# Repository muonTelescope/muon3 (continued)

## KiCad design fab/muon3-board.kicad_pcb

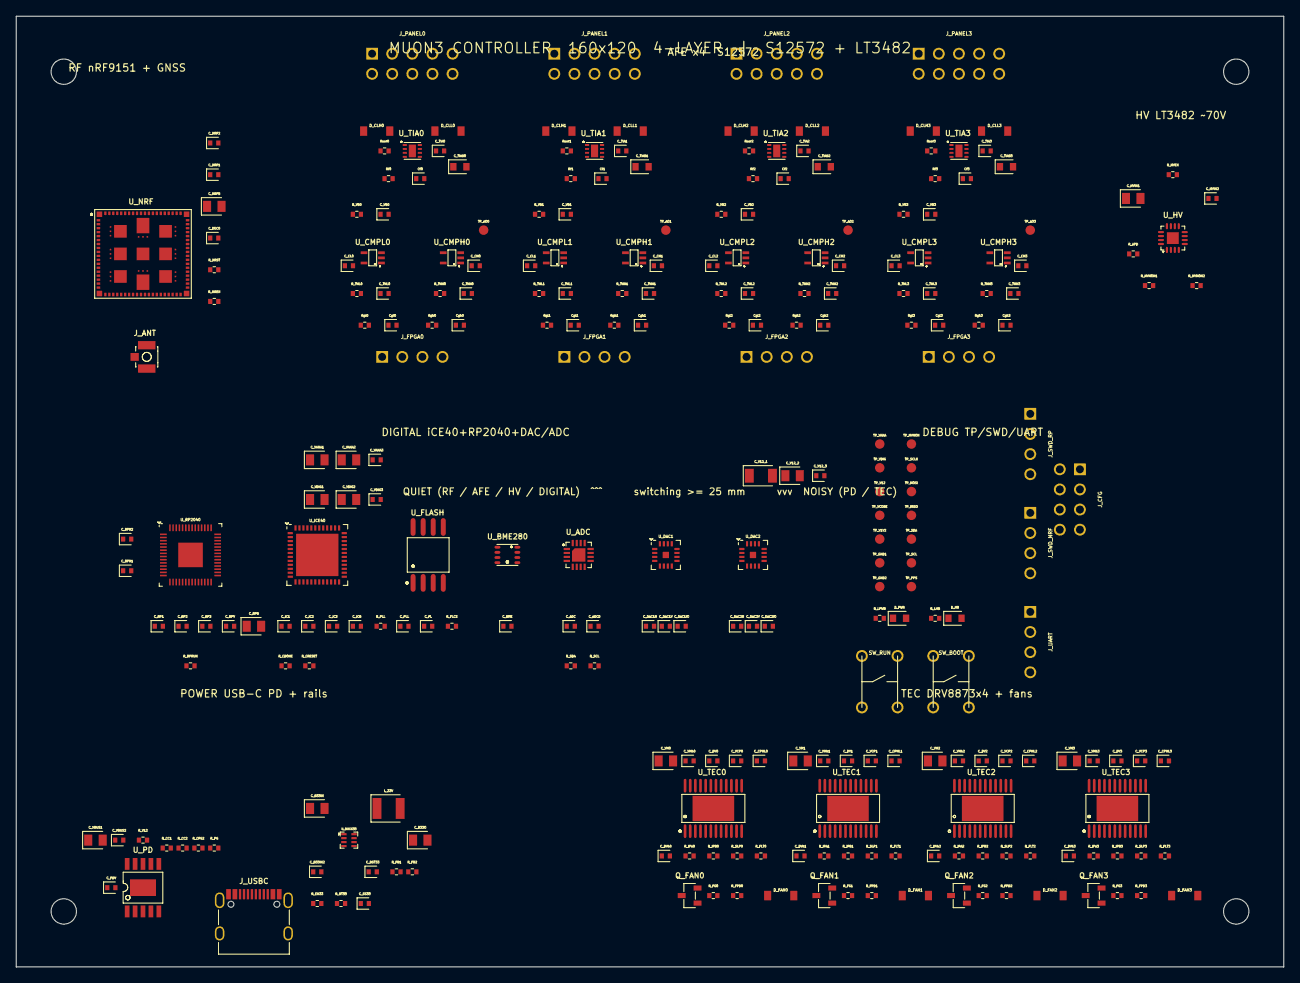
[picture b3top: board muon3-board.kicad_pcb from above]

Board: 4 copper layers, 160.0 x 120.0 mm, 265 parts (0 on the bottom side), 156 nets, no tracks yet.

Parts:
C_ADC: 100nF; capacitor_0402
C_ADCD: 1uF; capacitor_0402
C_B33IN: 10uF; capacitor_0805
C_B33IN2: 100nF; capacitor_0402
C_B33O: 22uF; capacitor_0805
C_BME: 100nF; capacitor_0402
C_BST33: 100nF; capacitor_0402
C_CH0, C_CH1, C_CH2, C_CH3: 100nF; capacitor_0402
C_CL0, C_CL1, C_CL2, C_CL3: 100nF; capacitor_0402
C_CPHL0, C_CPHL1, C_CPHL2, C_CPHL3: 47nF; capacitor_0402
C_DAC1IO, C_DAC1V, C_DAC2IO, C_DAC2V: 100nF; capacitor_0402
C_DAC1R, C_DAC2R: 1uF; capacitor_0402
C_DEC0: 100nF; capacitor_0402
C_DV0, C_DV1, C_DV2, C_DV3: 1uF; capacitor_0402
C_DVh0, C_DVh1, C_DVh2, C_DVh3: 100nF; capacitor_0402
C_FL: 100nF; capacitor_0402
C_HVIN1: 10uF; capacitor_0805
C_HVIN2: 100nF; capacitor_0402
C_IC1, C_IC2, C_IC3: 100nF; capacitor_0402
C_ICB: 1uF; capacitor_0402
C_NRF1, C_NRF2: 100nF; capacitor_0402
C_NRFB: 4.7uF; capacitor_0805
C_PDV: 100nF; capacitor_0402
C_PLL: 100nF; capacitor_0402
C_RP1, C_RP2, C_RP3: 100nF; capacitor_0402
C_RPB: 10uF; capacitor_0805
C_RPV: 1uF; capacitor_0402
C_RPX1, C_RPX2: 18pF; capacitor_0402
C_SS33: 10nF; capacitor_0402
C_THH0, C_THH1, C_THH2, C_THH3: 100nF; capacitor_0402
C_THL0, C_THL1, C_THL2, C_THL3: 100nF; capacitor_0402
C_TIA0, C_TIA1, C_TIA2, C_TIA3: 100nF; capacitor_0402
C_TIAB0, C_TIAB1, C_TIAB2, C_TIAB3: 2.2uF; capacitor_0603
C_V12_1: 22uF; capacitor_1206
C_V12_2: 10uF; capacitor_0805
C_V12_3: 100nF; capacitor_0402
C_VANA1, C_VANA2: 10uF; capacitor_0805
C_VANA3: 100nF; capacitor_0402
C_VB0, C_VB1, C_VB2, C_VB3: 100nF; capacitor_0402
C_VBUS1: 10uF; capacitor_0805
C_VBUS2: 100nF; capacitor_0402
C_VCP0, C_VCP1, C_VCP2, C_VCP3: 1uF; capacitor_0402
C_VDIG1, C_VDIG2: 10uF; capacitor_0805
C_VDIG3: 100nF; capacitor_0402
C_VM0, C_VM1, C_VM2, C_VM3: 10uF; capacitor_0805
C_VMh0, C_VMh1, C_VMh2, C_VMh3: 100nF; capacitor_0402
Cf0, Cf1, Cf2, Cf3: 1.5pF; capacitor_0402
Cgh0, Cgh1, Cgh2, Cgh3: 6pF; capacitor_0402
Cgl0, Cgl1, Cgl2, Cgl3: 6pF; capacitor_0402
D_CLH0, D_CLH1, D_CLH2, D_CLH3: D; diode_sod123
D_CLL0, D_CLL1, D_CLL2, D_CLL3: D; diode_sod123
D_FAN0, D_FAN1, D_FAN2, D_FAN3: D; diode_sod123
D_HB: LED; led_0603
D_PWR: LED; led_0603
J_ANT: BWU_FL_IPEX1
J_CFG: J_CFG; pin_header_pinrow8_nopinlabels_rows2
J_FPGA0: J_FPGA0; pin_header_pinrow4_nopinlabels
J_FPGA1: J_FPGA1; pin_header_pinrow4_nopinlabels
J_FPGA2: J_FPGA2; pin_header_pinrow4_nopinlabels
J_FPGA3: J_FPGA3; pin_header_pinrow4_nopinlabels
J_PANEL0: J_PANEL0; pin_header_pinrow10_nopinlabels_female_rows2
J_PANEL1: J_PANEL1; pin_header_pinrow10_nopinlabels_female_rows2
J_PANEL2: J_PANEL2; pin_header_pinrow10_nopinlabels_female_rows2
J_PANEL3: J_PANEL3; pin_header_pinrow10_nopinlabels_female_rows2
J_SWD_NRF: J_SWD_NRF; pin_header_pinrow4_nopinlabels
J_SWD_RP: J_SWD_RP; pin_header_pinrow4_nopinlabels
J_UART: J_UART; pin_header_pinrow4_nopinlabels
J_USBC: TYPE_C_31_M_12
L_33V: 4.7µH; inductor_1210
Q_FAN0, Q_FAN1, Q_FAN2, Q_FAN3: AO3400A
R_APD: 20Ω; resistor_res0402
R_CC1, R_CC2: 5.1kΩ; resistor_res0402
R_CDONE: 10kΩ; resistor_res0402
R_CFG2: 6.8kΩ; resistor_res0402
R_CRESET: 10kΩ; resistor_res0402
R_EN33: 100kΩ; resistor_res0402
R_FB1: 100kΩ; resistor_res0402
R_FB2: 32kΩ; resistor_res0402
R_FG0, R_FG1, R_FG2, R_FG3: 100Ω; resistor_res0402
R_FLCS: 10kΩ; resistor_res0402
R_FLT0, R_FLT1, R_FLT2, R_FLT3: 47kΩ; resistor_res0402
R_FPD0, R_FPD1, R_FPD2, R_FPD3: 10kΩ; resistor_res0402
R_HVEN: 100kΩ; resistor_res0402
R_HVMON1: 2MΩ; resistor_res0402
R_HVMON2: 51kΩ; resistor_res0402
R_IPA0, R_IPA1, R_IPA2, R_IPA3: 1.5kΩ; resistor_res0402
R_IPB0, R_IPB1, R_IPB2, R_IPB3: 1.5kΩ; resistor_res0402
R_LHB: 330Ω; resistor_res0402
R_LPWR: 1kΩ; resistor_res0402
R_NREN: 100kΩ; resistor_res0402
R_NRST: 10kΩ; resistor_res0402
R_PG: 10kΩ; resistor_res0402
R_PLL: 100Ω; resistor_res0402
R_RPRUN: 10kΩ; resistor_res0402
R_RT33: 100kΩ; resistor_res0402
R_SCL: 4.7kΩ; resistor_res0402
R_SDA: 4.7kΩ; resistor_res0402
R_SLP0, R_SLP1, R_SLP2, R_SLP3: 100kΩ; resistor_res0402
R_THH0, R_THH1, R_THH2, R_THH3: 1kΩ; resistor_res0402
R_THL0, R_THL1, R_THL2, R_THL3: 1kΩ; resistor_res0402
R_V12: 0Ω; resistor_res0402
R_VB0, R_VB1, R_VB2, R_VB3: 1kΩ; resistor_res0402
Rf0, Rf1, Rf2, Rf3: 15kΩ; resistor_res0402
Rgh0, Rgh1, Rgh2, Rgh3: 33Ω; resistor_res0402
Rgl0, Rgl1, Rgl2, Rgl3: 33Ω; resistor_res0402
Rser0, Rser1, Rser2, Rser3: 10Ω; resistor_res0402
SW_BOOT: SW_BOOT; push_button_pushbutton
SW_RUN: SW_RUN; push_button_pushbutton
TP_AO0: TP_AO0; test_point_smtpad_circle_d1.2
TP_AO1: TP_AO1; test_point_smtpad_circle_d1.2
TP_AO2: TP_AO2; test_point_smtpad_circle_d1.2
TP_AO3: TP_AO3; test_point_smtpad_circle_d1.2
TP_GND1: TP_GND1; test_point_smtpad_circle_d1.2
TP_GND2: TP_GND2; test_point_smtpad_circle_d1.2
TP_HVMON: TP_HVMON; test_point_smtpad_circle_d1.2
TP_MISO: TP_MISO; test_point_smtpad_circle_d1.2
TP_MOSI: TP_MOSI; test_point_smtpad_circle_d1.2
TP_PPS: TP_PPS; test_point_smtpad_circle_d1.2
TP_SCL: TP_SCL; test_point_smtpad_circle_d1.2
TP_SCLK: TP_SCLK; test_point_smtpad_circle_d1.2
TP_SDA: TP_SDA; test_point_smtpad_circle_d1.2
TP_V1V2: TP_V1V2; test_point_smtpad_circle_d1.2
TP_V12: TP_V12; test_point_smtpad_circle_d1.2
TP_VANA: TP_VANA; test_point_smtpad_circle_d1.2
TP_VCORE: TP_VCORE; test_point_smtpad_circle_d1.2
TP_VDIG: TP_VDIG; test_point_smtpad_circle_d1.2
U_ADC: ADS7128IRTER
U_BME280: BME280
U_BUCK33: TPS62933DRLR
U_CMPH0, U_CMPH1, U_CMPH2, U_CMPH3: TLV3601DCKR
U_CMPL0, U_CMPL1, U_CMPL2, U_CMPL3: TLV3601DCKR
U_DAC1, U_DAC2: DAC80508MRTER
U_FLASH: W25Q128JVSIQ
U_HV: LT3482EUD_TRPBF
U_ICE40: ICE40UP5K_SG48I
U_NRF: nRF9151_LACA_R7
U_PD: CH224K
U_RP2040: RP2040
U_TEC0, U_TEC1, U_TEC2, U_TEC3: DRV8873HPWPR
U_TIA0, U_TIA1, U_TIA2, U_TIA3: OPA858IDSGR

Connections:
ADC_DECAP: C_ADCD.1, U_ADC.8
AOUT0: TP_AO0.1, U_CMPH0.3, U_CMPL0.3, U_TIA0.6
AOUT1: TP_AO1.1, U_CMPH1.3, U_CMPL1.3, U_TIA1.6
AOUT2: TP_AO2.1, U_CMPH2.3, U_CMPL2.3, U_TIA2.6
AOUT3: TP_AO3.1, U_CMPH3.3, U_CMPL3.3, U_TIA3.6
BST33: C_BST33.1, U_BUCK33.6
CC1: J_USBC.6, R_CC1.1, U_PD.7
CC2: J_USBC.12, R_CC2.1, U_PD.6
CMPH0: Rgh0.1, U_CMPH0.1
CMPH1: Rgh1.1, U_CMPH1.1
CMPH2: Rgh2.1, U_CMPH2.1
CMPH3: Rgh3.1, U_CMPH3.1
CMPL0: Rgl0.1, U_CMPL0.1
CMPL1: Rgl1.1, U_CMPL1.1
CMPL2: Rgl2.1, U_CMPL2.1
CMPL3: Rgl3.1, U_CMPL3.1
CPH0: C_CPHL0.1, U_TEC0.22
CPH1: C_CPHL1.1, U_TEC1.22
CPH2: C_CPHL2.1, U_TEC2.22
CPH3: C_CPHL3.1, U_TEC3.22
CPL0: C_CPHL0.2, U_TEC0.23
CPL1: C_CPHL1.2, U_TEC1.23
CPL2: C_CPHL2.2, U_TEC2.23
CPL3: C_CPHL3.2, U_TEC3.23
DAC1_CS: U_DAC1.12, U_RP2040.28
DAC1_O3: C_DAC1R.1, U_DAC1.1
DAC2_CS: U_DAC2.12, U_RP2040.31
DAC2_O3: C_DAC2R.1, U_DAC2.1
DVDD0: C_DV0.1, C_DVh0.1, R_FLT0.1, R_SLP0.1, U_TEC0.1
DVDD1: C_DV1.1, C_DVh1.1, R_FLT1.1, R_SLP1.1, U_TEC1.1
DVDD2: C_DV2.1, C_DVh2.1, R_FLT2.1, R_SLP2.1, U_TEC2.1
DVDD3: C_DV3.1, C_DVh3.1, R_FLT3.1, R_SLP3.1, U_TEC3.1
EN33: R_EN33.2, U_BUCK33.2
FANG0: Q_FAN0.1, R_FG0.2, R_FPD0.1
FANG1: Q_FAN1.1, R_FG1.2, R_FPD1.1
FANG2: Q_FAN2.1, R_FG2.2, R_FPD2.1
FANG3: Q_FAN3.1, R_FG3.2, R_FPD3.1
FANN0: D_FAN0.1, J_PANEL0.10, Q_FAN0.3
FANN1: D_FAN1.1, J_PANEL1.10, Q_FAN1.3
FANN2: D_FAN2.1, J_PANEL2.10, Q_FAN2.3
FANN3: D_FAN3.1, J_PANEL3.10, Q_FAN3.3
FAULT0: R_FLT0.2, U_TEC0.2
FAULT1: R_FLT1.2, U_TEC1.2
FAULT2: R_FLT2.2, U_TEC2.2
FAULT3: R_FLT3.2, U_TEC3.2
FB0: Cf0.1, Rf0.1, U_TIA0.1
FB1: Cf1.1, Rf1.1, U_TIA1.1
FB2: Cf2.1, Rf2.1, U_TIA2.1
FB3: Cf3.1, Rf3.1, U_TIA3.1
FB33: R_FB1.2, R_FB2.1, U_BUCK33.8
FLASH_CS: R_FLCS.2, SW_BOOT.1, U_FLASH.1, U_RP2040.56
FPAH0: Cgh0.1, J_FPGA0.2, Rgh0.2, U_ICE40.47
FPAH1: Cgh1.1, J_FPGA1.2, Rgh1.2, U_ICE40.45
FPAH2: Cgh2.1, J_FPGA2.2, Rgh2.2, U_ICE40.4
FPAH3: Cgh3.1, J_FPGA3.2, Rgh3.2, U_ICE40.6
FPAL0: Cgl0.1, J_FPGA0.1, Rgl0.2, U_ICE40.46
FPAL1: Cgl1.1, J_FPGA1.1, Rgl1.2, U_ICE40.48
FPAL2: Cgl2.1, J_FPGA2.1, Rgl2.2, U_ICE40.2
FPAL3: Cgl3.1, J_FPGA3.1, Rgl3.2, U_ICE40.3
GND: C_ADC.2, C_ADCD.2, C_B33IN.2, C_B33IN2.2, C_B33O.2, C_BME.2, C_CH0.2, C_CH1.2, C_CH2.2, C_CH3.2, C_CL0.2, C_CL1.2, C_CL2.2, C_CL3.2, C_DAC1IO.2, C_DAC1R.2, C_DAC1V.2, C_DAC2IO.2, C_DAC2R.2, C_DAC2V.2, C_DEC0.2, C_DV0.2, C_DV1.2, C_DV2.2, C_DV3.2, C_DVh0.2, C_DVh1.2, C_DVh2.2, C_DVh3.2, C_FL.2, C_HVIN1.2, C_HVIN2.2, C_IC1.2, C_IC2.2, C_IC3.2, C_ICB.2, C_NRF1.2, C_NRF2.2, C_NRFB.2, C_PDV.2, C_PLL.2, C_RP1.2, C_RP2.2, C_RP3.2, C_RPB.2, C_RPV.2, C_RPX1.2, C_RPX2.2, C_SS33.2, C_THH0.2, C_THH1.2, C_THH2.2, C_THH3.2, C_THL0.2, C_THL1.2, C_THL2.2, C_THL3.2, C_TIA0.2, C_TIA1.2, C_TIA2.2, C_TIA3.2, C_TIAB0.2, C_TIAB1.2, C_TIAB2.2, C_TIAB3.2, C_V12_1.2, C_V12_2.2, C_V12_3.2, C_VANA1.2, C_VANA2.2, C_VANA3.2, C_VB0.2, C_VB1.2, C_VB2.2, C_VB3.2, C_VBUS1.2, C_VBUS2.2, C_VDIG1.2, C_VDIG2.2, C_VDIG3.2, C_VM0.2, C_VM1.2, C_VM2.2, C_VM3.2, C_VMh0.2, C_VMh1.2, C_VMh2.2, C_VMh3.2, Cgh0.2, Cgh1.2, Cgh2.2, Cgh3.2, Cgl0.2, Cgl1.2, Cgl2.2, Cgl3.2, D_CLL0.1, D_CLL1.1, D_CLL2.1, D_CLL3.1, D_HB.2, D_PWR.2, J_ANT.2, J_ANT.3, J_CFG.8, J_FPGA0.3, J_FPGA0.4, J_FPGA1.3, J_FPGA1.4, J_FPGA2.3, J_FPGA2.4, J_FPGA3.3, J_FPGA3.4, J_PANEL0.2, J_PANEL0.4, J_PANEL1.2, J_PANEL1.4, J_PANEL2.2, J_PANEL2.4, J_PANEL3.2, J_PANEL3.4, J_SWD_NRF.3, J_SWD_RP.3, J_UART.4, J_USBC.1, J_USBC.2, J_USBC.3, J_USBC.4, J_USBC.13, J_USBC.14, Q_FAN0.2, Q_FAN1.2, Q_FAN2.2, Q_FAN3.2, R_CC1.2, R_CC2.2, R_CFG2.2, R_FB2.2, R_FPD0.2, R_FPD1.2, R_FPD2.2, R_FPD3.2, R_HVMON2.2, R_IPA0.2, R_IPA1.2, R_IPA2.2, R_IPA3.2, R_IPB0.2, R_IPB1.2, R_IPB2.2, R_IPB3.2, R_RT33.2, SW_BOOT.2, SW_RUN.2, TP_GND1.1, TP_GND2.1, U_ADC.9, U_ADC.11, U_ADC.17, U_BME280.1, U_BME280.5, U_BME280.7, U_BUCK33.4, U_CMPH0.2, U_CMPH1.2, U_CMPH2.2, U_CMPH3.2, U_CMPL0.2, U_CMPL1.2, U_CMPL2.2, U_CMPL3.2, U_DAC1.6, U_DAC1.17, U_DAC2.6, U_DAC2.17, U_FLASH.4, U_HV.9, U_HV.10, U_HV.17, U_ICE40.49, U_NRF.1, U_NRF.7, U_NRF.13, U_NRF.15, U_NRF.20, U_NRF.25, U_NRF.30, U_NRF.34, U_NRF.36, U_NRF.38, U_NRF.39, U_NRF.40, U_NRF.41, U_NRF.43, U_NRF.46, U_NRF.51, U_NRF.55, U_NRF.60, U_NRF.66, U_NRF.71, U_NRF.76, U_NRF.105, U_NRF.106, U_NRF.107, U_NRF.108, U_NRF.109, U_NRF.110, U_NRF.111, U_NRF.112, U_NRF.113, U_PD.11, U_RP2040.57, U_TEC0.16, U_TEC0.17, U_TEC0.24, U_TEC0.25, U_TEC1.16, U_TEC1.17, U_TEC1.24, U_TEC1.25, U_TEC2.16, U_TEC2.17, U_TEC2.24, U_TEC2.25, U_TEC3.16, U_TEC3.17, U_TEC3.24, U_TEC3.25, U_TIA0.5, U_TIA0.9, U_TIA1.5, U_TIA1.9, U_TIA2.5, U_TIA2.9, U_TIA3.5, U_TIA3.9
HV_APD: R_APD.1, U_HV.2
HV_BIAS: R_APD.2, R_HVMON1.1
HV_EN: R_HVEN.2, U_HV.12
HV_MON: R_HVMON1.2, R_HVMON2.1, TP_HVMON.1, U_HV.16
I2C_SCL: R_SCL.2, TP_SCL.1, U_ADC.13, U_BME280.4, U_RP2040.7
I2C_SDA: R_SDA.2, TP_SDA.1, U_ADC.14, U_BME280.3, U_RP2040.6
ICE_CDONE: J_CFG.7, R_CDONE.2, U_ICE40.7, U_RP2040.18
ICE_CRESET: J_CFG.6, R_CRESET.2, U_ICE40.8, U_RP2040.17
ICE_SCK: J_CFG.2, U_ICE40.15, U_RP2040.13
ICE_SI: J_CFG.3, U_ICE40.17, U_RP2040.14
ICE_SO: J_CFG.4, U_ICE40.14, U_RP2040.15
ICE_SS: J_CFG.5, U_ICE40.16, U_RP2040.16
INA0: Cf0.2, D_CLH0.1, D_CLL0.2, Rf0.2, Rser0.2, U_TIA0.3
INA1: Cf1.2, D_CLH1.1, D_CLL1.2, Rf1.2, Rser1.2, U_TIA1.3
INA2: Cf2.2, D_CLH2.1, D_CLL2.2, Rf2.2, Rser2.2, U_TIA2.3
INA3: Cf3.2, D_CLH3.1, D_CLL3.2, Rf3.2, Rser3.2, U_TIA3.3
IPA0: R_IPA0.1, U_TEC0.10
IPA1: R_IPA1.1, U_TEC1.10
IPA2: R_IPA2.1, U_TEC2.10
IPA3: R_IPA3.1, U_TEC3.10
IPB0: R_IPB0.1, U_TEC0.12
IPB1: R_IPB1.1, U_TEC1.12
IPB2: R_IPB2.1, U_TEC2.12
IPB3: R_IPB3.1, U_TEC3.12
LED_HB_A: D_HB.1, R_LHB.2
LED_PWR_A: D_PWR.1, R_LPWR.2
NRF_DEC0: C_DEC0.1, U_NRF.24
NRF_EN: R_NREN.2, U_NRF.10
NRF_RESET: J_SWD_NRF.4, R_NRST.2, U_NRF.9
NRF_SWDCLK: J_SWD_NRF.1, U_NRF.3
NRF_SWDIO: J_SWD_NRF.2, U_NRF.4
OA0: J_PANEL0.7, U_TEC0.18, U_TEC0.19
OA1: J_PANEL1.7, U_TEC1.18, U_TEC1.19
OA2: J_PANEL2.7, U_TEC2.18, U_TEC2.19
OA3: J_PANEL3.7, U_TEC3.18, U_TEC3.19
OB0: J_PANEL0.8, U_TEC0.14, U_TEC0.15
OB1: J_PANEL1.8, U_TEC1.14, U_TEC1.15
OB2: J_PANEL2.8, U_TEC2.14, U_TEC2.15
OB3: J_PANEL3.8, U_TEC3.14, U_TEC3.15
PD_CFG2: R_CFG2.1, U_PD.2
PD_PG: R_PG.2, U_PD.10
PD_VDD: C_PDV.1, R_PG.1, U_PD.1
PPS: TP_PPS.1, U_ICE40.9, U_NRF.21
QSPI_SCLK: U_FLASH.6, U_RP2040.52
QSPI_SD0: U_FLASH.5, U_RP2040.53
QSPI_SD1: U_FLASH.2, U_RP2040.55
QSPI_SD2: U_FLASH.3, U_RP2040.54
QSPI_SD3: U_FLASH.7, U_RP2040.51
RF_ANT: J_ANT.1, U_NRF.35
RP_LED: R_LHB.1, U_RP2040.37
RP_RUN: J_SWD_RP.4, R_RPRUN.2, SW_RUN.1, U_RP2040.26
RP_SWCLK: J_SWD_RP.1, U_RP2040.24
RP_SWD: J_SWD_RP.2, U_RP2040.25
RP_XIN: C_RPX1.1, U_RP2040.20
RP_XOUT: C_RPX2.1, U_RP2040.21
RT33: R_RT33.1, U_BUCK33.1
SIG0: J_PANEL0.1, Rser0.1
SIG1: J_PANEL1.1, Rser1.1
SIG2: J_PANEL2.1, Rser2.1
SIG3: J_PANEL3.1, Rser3.1
SLEEP0: R_SLP0.2, U_TEC0.11
SLEEP1: R_SLP1.2, U_TEC1.11
SLEEP2: R_SLP2.2, U_TEC2.11
SLEEP3: R_SLP3.2, U_TEC3.11
SPI_MISO: TP_MISO.1, U_RP2040.27
SPI_MOSI: TP_MOSI.1, U_DAC1.14, U_DAC2.14, U_RP2040.30
SPI_SCLK: TP_SCLK.1, U_DAC1.13, U_DAC2.13, U_RP2040.29
SS33: C_SS33.1, U_BUCK33.7
SW33: C_BST33.2, L_33V.1, U_BUCK33.5
UART_RX: J_UART.3, U_RP2040.3
UART_TX: J_UART.2, U_RP2040.2
USB_DM: J_USBC.10, U_PD.5, U_RP2040.46
USB_DP: J_USBC.8, U_PD.4, U_RP2040.47
V1V2: C_IC1.1, C_IC2.1, R_PLL.1, TP_V1V2.1, U_ICE40.5, U_ICE40.30
V1V2_PLL: C_PLL.1, R_PLL.2, U_ICE40.29
V12: C_B33IN.1, C_B33IN2.1, C_HVIN1.1, C_HVIN2.1, C_V12_1.1, C_V12_2.1, C_V12_3.1, C_VCP0.2, C_VCP1.2, C_VCP2.2, C_VCP3.2, C_VM0.1, C_VM1.1, C_VM2.1, C_VM3.1, C_VMh0.1, C_VMh1.1, C_VMh2.1, C_VMh3.1, D_FAN0.2, D_FAN1.2, D_FAN2.2, D_FAN3.2, J_PANEL0.9, J_PANEL1.9, J_PANEL2.9, J_PANEL3.9, R_EN33.1, R_HVEN.1, R_V12.2, TP_V12.1, U_BUCK33.3, U_HV.11, U_TEC0.13, U_TEC0.20, U_TEC1.13, U_TEC1.20, U_TEC2.13, U_TEC2.20, U_TEC3.13, U_TEC3.20
VANA: C_DAC1V.1, C_DAC2V.1, C_TIA0.1, C_TIA1.1, C_TIA2.1, C_TIA3.1, C_TIAB0.1, C_TIAB1.1, C_TIAB2.1, C_TIAB3.1, C_VANA1.1, C_VANA2.1, C_VANA3.1, D_CLH0.2, D_CLH1.2, D_CLH2.2, D_CLH3.2, TP_VANA.1, U_DAC1.7, U_DAC2.7, U_TIA0.7, U_TIA0.8, U_TIA1.7, U_TIA1.8, U_TIA2.7, U_TIA2.8, U_TIA3.7, U_TIA3.8
VBOTF0: C_VB0.1, R_VB0.2, U_TIA0.4
VBOTF1: C_VB1.1, R_VB1.2, U_TIA1.4
VBOTF2: C_VB2.1, R_VB2.2, U_TIA2.4
VBOTF3: C_VB3.1, R_VB3.2, U_TIA3.4
VBUS: C_VBUS1.1, C_VBUS2.1, J_USBC.15, J_USBC.16, R_V12.1, U_PD.8
VCORE: C_RPV.1, TP_VCORE.1, U_RP2040.23, U_RP2040.45, U_RP2040.50
VCP0: C_VCP0.1, U_TEC0.21
VCP1: C_VCP1.1, U_TEC1.21
VCP2: C_VCP2.1, U_TEC2.21
VCP3: C_VCP3.1, U_TEC3.21
VDIG: C_ADC.1, C_B33O.1, C_BME.1, C_CH0.1, C_CH1.1, C_CH2.1, C_CH3.1, C_CL0.1, C_CL1.1, C_CL2.1, C_CL3.1, C_DAC1IO.1, C_DAC2IO.1, C_FL.1, C_IC3.1, C_ICB.1, C_NRF1.1, C_NRF2.1, C_NRFB.1, C_RP1.1, C_RP2.1, C_RP3.1, C_RPB.1, C_VDIG1.1, C_VDIG2.1, C_VDIG3.1, J_CFG.1, J_UART.1, L_33V.2, R_CDONE.1, R_CRESET.1, R_FB1.1, R_FLCS.1, R_LPWR.1, R_NREN.1, R_NRST.1, R_RPRUN.1, R_SCL.1, R_SDA.1, TP_VDIG.1, U_ADC.7, U_ADC.10, U_BME280.2, U_BME280.6, U_BME280.8, U_CMPH0.5, U_CMPH1.5, U_CMPH2.5, U_CMPH3.5, U_CMPL0.5, U_CMPL1.5, U_CMPL2.5, U_CMPL3.5, U_DAC1.16, U_DAC2.16, U_FLASH.8, U_ICE40.1, U_ICE40.22, U_ICE40.24, U_ICE40.33, U_NRF.14, U_NRF.29, U_NRF.65, U_RP2040.1, U_RP2040.10, U_RP2040.22, U_RP2040.33, U_RP2040.42, U_RP2040.43, U_RP2040.44, U_RP2040.48, U_RP2040.49
VTHHF0: C_THH0.1, R_THH0.2, U_CMPH0.4
VTHHF1: C_THH1.1, R_THH1.2, U_CMPH1.4
VTHHF2: C_THH2.1, R_THH2.2, U_CMPH2.4
VTHHF3: C_THH3.1, R_THH3.2, U_CMPH3.4
VTHLF0: C_THL0.1, R_THL0.2, U_CMPL0.4
VTHLF1: C_THL1.1, R_THL1.2, U_CMPL1.4
VTHLF2: C_THL2.1, R_THL2.2, U_CMPL2.4
VTHLF3: C_THL3.1, R_THL3.2, U_CMPL3.4

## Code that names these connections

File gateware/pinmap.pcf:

# Muon3 iCE40UP5K-SG48 pinmap (using validated IO pins)
set_io clk_25m 21
set_io pps 20

set_io cmp_low_0  2
set_io cmp_high_0 3
set_io cmp_low_1  4
set_io cmp_high_1 6
set_io cmp_low_2  9
set_io cmp_high_2 10
set_io cmp_low_3  11
set_io cmp_high_3 12

set_io spi_sck   13
set_io spi_mosi  14
set_io spi_miso  15
set_io spi_cs_n  16

set_io debug[0]  17
set_io debug[1]  18
set_io debug[2]  19
set_io debug[3]  23

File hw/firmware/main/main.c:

// Bench acquisition prototype. Bias stays OFF until per-sensor calibration is
// implemented and reviewed; this firmware never asserts HV_EN.
#include <inttypes.h>
#include <stdio.h>
#include <string.h>
#include <stdatomic.h>
#include "driver/gpio.h"
#include "driver/spi_master.h"
#include "esp_event.h"
#include "esp_netif.h"
#include "esp_rom_sys.h"
#include "esp_timer.h"
#include "esp_wifi.h"
#include "freertos/FreeRTOS.h"
#include "freertos/queue.h"
#include "freertos/task.h"
#include "lwip/sockets.h"
#include "nvs_flash.h"
#include "muon_protocol.h"
#ifndef CONFIG_MUON_WIFI_SSID
#define CONFIG_MUON_WIFI_SSID ""
#endif

enum { HV_EN=12, INJ=13, CFG_CS=10, CFG_MOSI=11, CFG_SCK=14,
       CRESET=15, CDONE=16, SPI_CS=17, SPI_SCK=21, SPI_MOSI=38,
       SPI_MISO=39, IRQ=40, ACQ_RESET=41, MUX_RESET=42 };
extern const unsigned char muon_fpga_image[];
extern const size_t muon_fpga_image_size;
static spi_device_handle_t fpga;
static QueueHandle_t packets;
static atomic_uint_fast32_t software_drops, udp_errors;
static atomic_bool wifi_ready;
static uint32_t epoch;
typedef struct { uint32_t seq; uint8_t type, length, data[65]; } packet;

static void output(int pin, int value) {
    ESP_ERROR_CHECK(gpio_set_level(pin, value));
    ESP_ERROR_CHECK(gpio_set_direction(pin, GPIO_MODE_OUTPUT));
}
static void cfg_bit(int bit) {
    gpio_set_level(CFG_MOSI, bit);
    esp_rom_delay_us(1);
    gpio_set_level(CFG_SCK, 1);
    esp_rom_delay_us(1);
    gpio_set_level(CFG_SCK, 0);
}
static void program_fpga(void) {
    ESP_ERROR_CHECK(muon_fpga_image_size > 1000 ? ESP_OK : ESP_ERR_INVALID_SIZE);
    // SPI slave configuration: hold SS low across CRESET rising, wait 1.2ms,
    // eight clocks with SS high, image with SS low, then 49 trailing clocks.
    output(CFG_SCK, 0); output(CFG_MOSI, 0); output(CFG_CS, 0);
    output(CRESET, 0);
    ESP_ERROR_CHECK(gpio_set_direction(CDONE, GPIO_MODE_INPUT));
    esp_rom_delay_us(10);
    gpio_set_level(CRESET, 1); esp_rom_delay_us(1300);
    gpio_set_level(CFG_CS, 1);
    for (int i = 0; i < 8; ++i) cfg_bit(0);
    gpio_set_level(CFG_CS, 0);
    for (size_t i = 0; i < muon_fpga_image_size; ++i) {
        for (int bit = 7; bit >= 0; --bit) cfg_bit((muon_fpga_image[i] >> bit) & 1);
        if ((i & 4095) == 4095) vTaskDelay(1);
    }
    gpio_set_level(CFG_CS, 1);
    for (int i = 0; i < 64; ++i) cfg_bit(0);
    ESP_ERROR_CHECK(gpio_get_level(CDONE) ? ESP_OK : ESP_FAIL);
}
static void exchange(uint8_t command, uint8_t *rx, size_t n) {
    uint8_t tx[65] = {0}; tx[0] = command;
    spi_transaction_t t = {.length=n*8, .tx_buffer=tx, .rx_buffer=rx};
    // Manual CS enforces setup/hold even across differing acquisition clocks.
    gpio_set_level(SPI_CS, 0); esp_rom_delay_us(1);
    esp_err_t err = spi_device_polling_transmit(fpga, &t);
    esp_rom_delay_us(1); gpio_set_level(SPI_CS, 1); esp_rom_delay_us(1);
    ESP_ERROR_CHECK(err);
}
static void queue_packet(uint8_t type, const uint8_t *data, int length, uint32_t seq) {
    packet p = {.seq=seq, .type=type, .length=length};
    memcpy(p.data, data, length);
    if (xQueueSend(packets, &p, 0) != pdPASS) atomic_fetch_add(&software_drops, 1);
}
static void acquire(void *unused) {
    (void)unused;
    uint32_t sequence = 0;
    int64_t next_status = 0;
    for (;;) {
        // Bounded batches yield to housekeeping even under continuous noise.
        for (int n = 0; n < 64 && gpio_get_level(IRQ); ++n) {
            uint8_t rx[26]; exchange(MUON_READ_EVENT, rx, sizeof(rx));
            muon_event event;
            if (muon_decode_event(rx, sizeof(rx), &event))
                queue_packet(1, rx, sizeof(rx), sequence++);
        }
        if (esp_timer_get_time() >= next_status) {
            uint8_t rx[65]; exchange(MUON_READ_STATUS, rx, sizeof(rx));
            muon_status status;
            ESP_ERROR_CHECK(muon_decode_status(rx, sizeof(rx), &status) ? ESP_OK : ESP_FAIL);
            queue_packet(2, rx, sizeof(rx), sequence++);
            next_status = esp_timer_get_time() + 1000000;
        }
        vTaskDelay(1);
    }
}
static void wifi_event(void *arg, esp_event_base_t base, int32_t id, void *data) {
    (void)arg; (void)data;
    if (base == WIFI_EVENT && id == WIFI_EVENT_STA_START) esp_wifi_connect();
    else if (base == WIFI_EVENT && id == WIFI_EVENT_STA_DISCONNECTED) {
        atomic_store(&wifi_ready, false); esp_wifi_connect();
    } else if (base == IP_EVENT && id == IP_EVENT_STA_GOT_IP) atomic_store(&wifi_ready, true);
}
static void start_wifi(void) {
#ifndef CONFIG_MUON_POWER_BUDGET_VERIFIED
    return;
#endif
    if (!strlen(CONFIG_MUON_WIFI_SSID)) return;
    ESP_ERROR_CHECK(esp_netif_init());
    ESP_ERROR_CHECK(esp_event_loop_create_default());
    esp_netif_create_default_wifi_sta();
    wifi_init_config_t init = WIFI_INIT_CONFIG_DEFAULT();
    ESP_ERROR_CHECK(esp_wifi_init(&init));
    ESP_ERROR_CHECK(esp_event_handler_register(WIFI_EVENT, ESP_EVENT_ANY_ID, wifi_event, NULL));
    ESP_ERROR_CHECK(esp_event_handler_register(IP_EVENT, IP_EVENT_STA_GOT_IP, wifi_event, NULL));
    wifi_config_t cfg = {0};
    snprintf((char *)cfg.sta.ssid, sizeof(cfg.sta.ssid), "%s", CONFIG_MUON_WIFI_SSID);
    snprintf((char *)cfg.sta.password, sizeof(cfg.sta.password), "%s", CONFIG_MUON_WIFI_PASSWORD);
    ESP_ERROR_CHECK(esp_wifi_set_mode(WIFI_MODE_STA));
    ESP_ERROR_CHECK(esp_wifi_set_config(WIFI_IF_STA, &cfg));
    ESP_ERROR_CHECK(esp_wifi_start());
}
static void stream(void *unused) {
    (void)unused;
    int sock = -1;
    struct sockaddr_in destination = {.sin_family=AF_INET, .sin_port=htons(CONFIG_MUON_UDP_PORT)};
    if (strlen(CONFIG_MUON_UDP_HOST) && inet_pton(AF_INET, CONFIG_MUON_UDP_HOST, &destination.sin_addr) == 1) {
        sock = socket(AF_INET, SOCK_DGRAM, IPPROTO_UDP);
        if (sock >= 0) {
            struct timeval timeout = {.tv_usec=10000};
            setsockopt(sock, SOL_SOCKET, SO_SNDTIMEO, &timeout, sizeof(timeout));
        }
    }
    packet p;
    for (;;) {
        if (xQueueReceive(packets, &p, portMAX_DELAY) != pdPASS) continue;
        char hex[131], line[400];
        for (int i = 0; i < p.length; ++i) snprintf(hex + i*2, 3, "%02x", p.data[i]);
        int count = snprintf(line, sizeof(line),
            "{\"v\":1,\"epoch\":%"PRIu32",\"seq\":%"PRIu32",\"type\":%u,\"spi_hex\":\"%s\",\"software_drops\":%lu,\"udp_errors\":%lu,\"bias_enabled\":false}\n",
            epoch, p.seq, p.type, hex, (unsigned long)atomic_load(&software_drops), (unsigned long)atomic_load(&udp_errors));
        if (sock >= 0 && atomic_load(&wifi_ready)) {
            if (sendto(sock, line, count, 0, (struct sockaddr *)&destination, sizeof(destination)) != count)
                atomic_fetch_add(&udp_errors, 1);
        }
        // USB may stall this low-priority consumer, never the acquisition task.
        fwrite(line, 1, count, stdout); fflush(stdout);
    }
}
void app_main(void) {
    output(HV_EN, 0); output(INJ, 0); output(ACQ_RESET, 1); output(MUX_RESET, 0);
    output(SPI_CS, 1);
    ESP_ERROR_CHECK(gpio_set_direction(IRQ, GPIO_MODE_INPUT));
    ESP_ERROR_CHECK(nvs_flash_init());
    program_fpga();
    spi_bus_config_t bus = {.mosi_io_num=SPI_MOSI, .miso_io_num=SPI_MISO,
        .sclk_io_num=SPI_SCK, .quadwp_io_num=-1, .quadhd_io_num=-1, .max_transfer_sz=65};
    ESP_ERROR_CHECK(spi_bus_initialize(SPI2_HOST, &bus, SPI_DMA_DISABLED));
    spi_device_interface_config_t device = {.clock_speed_hz=1000000, .mode=0, .spics_io_num=-1, .queue_size=1};
    ESP_ERROR_CHECK(spi_bus_add_device(SPI2_HOST, &device, &fpga));
    gpio_set_level(ACQ_RESET, 0); esp_rom_delay_us(10);
    uint8_t rx[65]; exchange(MUON_READ_STATUS, rx, sizeof(rx));
    muon_status status;
    ESP_ERROR_CHECK(muon_decode_status(rx, sizeof(rx), &status) ? ESP_OK : ESP_FAIL);
    exchange(MUON_RESET, rx, 2);
    ESP_ERROR_CHECK(rx[1] == 0xac ? ESP_OK : ESP_FAIL);
    epoch = (uint32_t)esp_timer_get_time();
    packets = xQueueCreate(128, sizeof(packet));
    ESP_ERROR_CHECK(packets ? ESP_OK : ESP_ERR_NO_MEM);
    start_wifi();
    xTaskCreatePinnedToCore(acquire, "capture", 4096, NULL, 12, NULL, 1);
    xTaskCreatePinnedToCore(stream, "stream", 4096, NULL, 4, NULL, 0);
}
